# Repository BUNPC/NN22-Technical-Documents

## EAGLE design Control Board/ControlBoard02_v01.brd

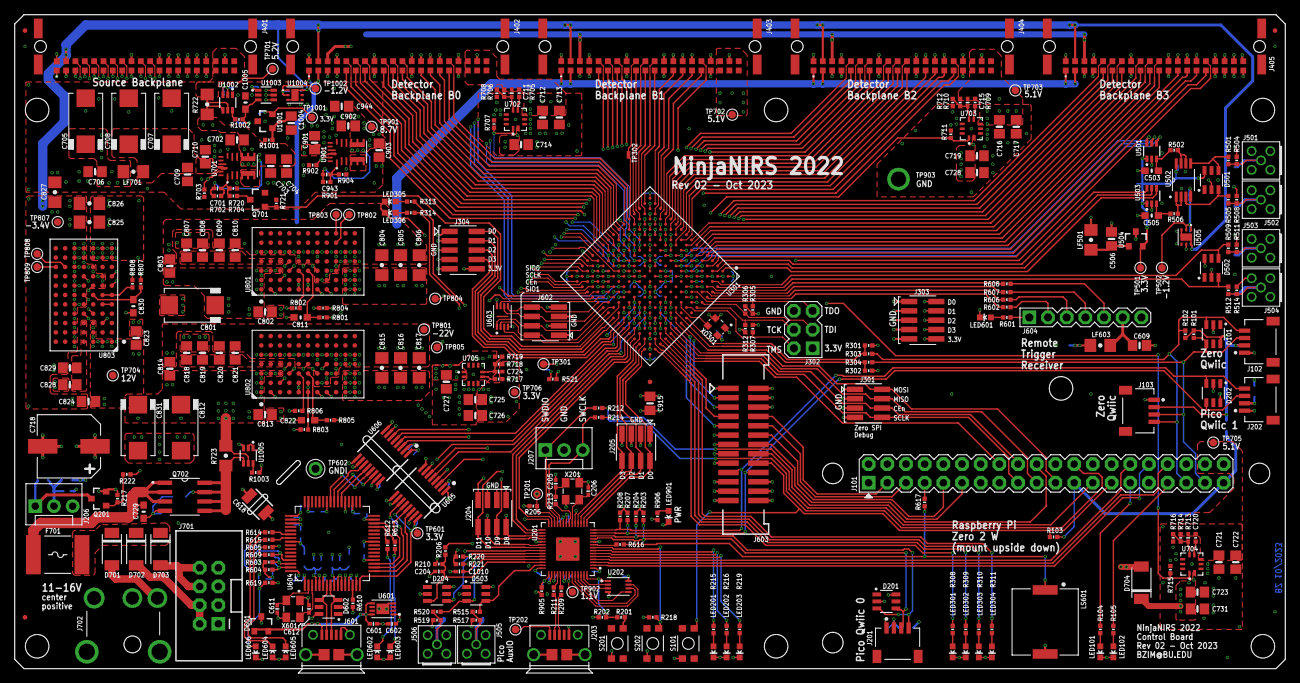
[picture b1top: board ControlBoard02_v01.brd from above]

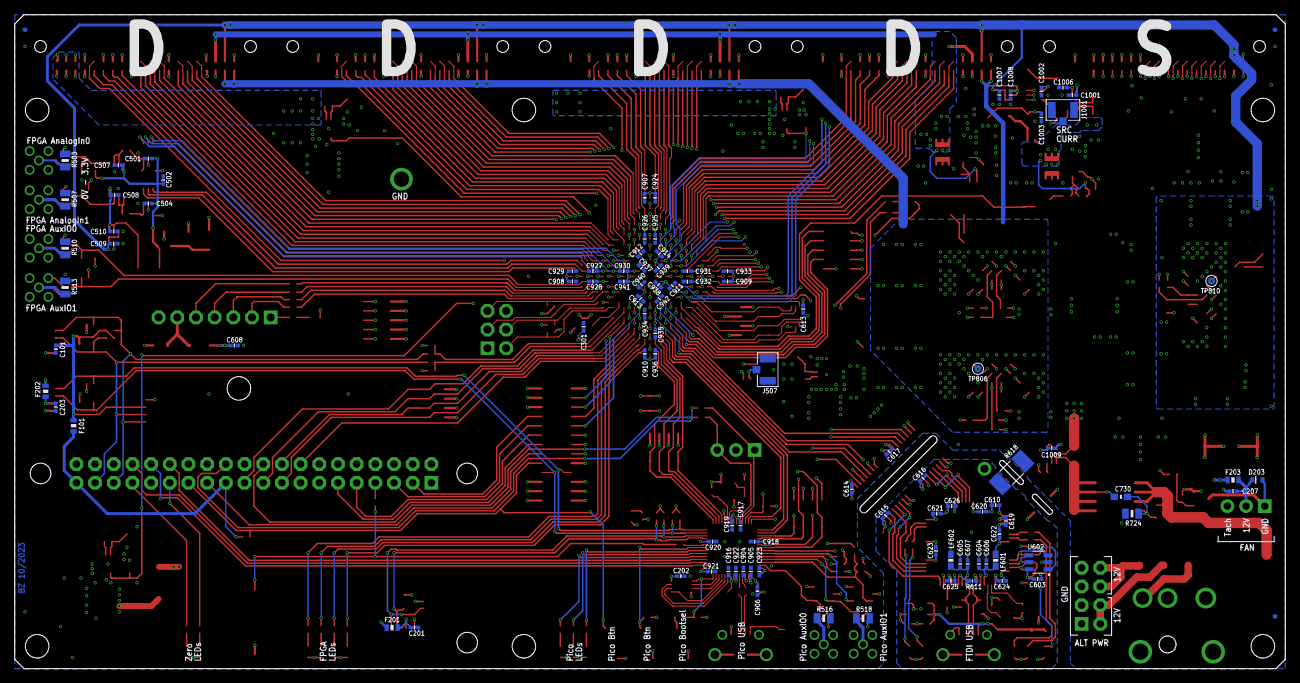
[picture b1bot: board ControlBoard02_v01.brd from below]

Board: 6 copper layers, 172.7 x 88.9 mm, 430 parts (103 on the bottom side), 365 nets.

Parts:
C101, C201, C202, C203, C204, C207, C301, C501, C504, C507, C508, C603, C606, C607, C608, C613, C614, C615, C616, C617, C619, C620, C621, C622, C623, C624, C625, C626, C916, C917, C918, C919, C920, C921, C922, C923, C924, C925, C926, C927, C928, C929, C930, C931, C932, C933, C934, C935, C936, C937, C938, C939, C940, C941, C942, C1001, C1002, C1006, C1009, C1010: 0.1u; 0402-CAP
C205, C206, C611, C612: 27p; 0402-CAP
C502, C509, C510, C601, C602, C604, C605, C610, C904, C905, C906, C907, C908, C909, C910, C911, C912, C913, C914, C1003, C1007, C1008: 4.7u; 0402-CAP
C503, C505, C729, C1005: 10n; 0603-CAP
C506, C609, C702, C703, C704, C706, C709, C710, C712, C713, C714, C716, C717, C719, C721, C722, C723, C725, C726, C727, C728, C731, C901, C902, C903, C944, C1004: 22u; 0805-CAP
C618: DNP; 1210
C701, C943: 22p; 0402-CAP
C705, C707, C708, C801, C812, C831: 100u/25V; 2917-CAP
C711, C715, C720, C724: 39p; 0402-CAP
C718: 330u/25V; CAP-SMD-POL-8X10
C730: 1n; 0603-CAP
C802, C803, C807, C808, C809, C810, C813, C814, C818, C819, C820, C821, C823, C824, C828, C829: 4.7u; 0805-CAP
C804, C805, C806, C815, C816, C817: 10u; 1206
C811, C822, C830: 1u; 0603-CAP
C825, C826: 100u; 1206
C827: DNP; 1206
C915: DNP; 0805-CAP
D101, D201, D202, D204, D501, D502, D503, D602: D1213A-02SO; SOT23-6
D203: SOD523
D601: PACDN042; SOT23-3
D701, D702, D703, D704: SOD128
F101, F201, F202, F203: 0ZCM0010FF2G; 0603-RES
F701: 2920L600/16MR; 2920-FUSE
FID901, FID902, FID903, FID904, FID905, FID906, FID907: FIDUCIALUFIDUCIAL; MICRO-FIDUCIAL
J101: M20X2_PTH
J102, J103, J201, J202: M04X1_JST_SH_RA; M04X1_JST_SH_SM_RA
J203, J601: USB-MICRO
J204, J205, J301, J602: M04X2_0.050_SMD_NO_CREAM
J206, J207: MOLEX-1X3
J302: M03X2PTH; 2X3-NS
J303, J304: M05X2_SMD_0.050_NOCREAM; M05X2_0.050_SMD_NO_CREAM
J401, J402, J403, J404, J405: M20X2_HARFLEX_M
J501, J502, J503, J504, J505, J506: SMA_MMCX_PTH_RA; MMCX_PTH_RA
J507, J1001: U.FL
J603: M13X2_0.050_SHF_NO_CREAM
J604: M07X1_PTH
J701: M04X2_SHROUDED; M04X2-SHROUDED
J702: POWERJACK_PJ051AH; PJ051AH
LED101, LED201, LED301, LED303, LED305, LED603, LED605, LED606, LED901: LTST-C191KRKT; LED-0603
LED102, LED202, LED203, LED302, LED304, LED306, LED601, LED602, LED604: LTST-C191KGKT; LED-0603
LF501, LF603, LF701: FERRITE1206; 1206
LF601, LF602: FERRITE0603; 0603-FER
LS601: PKMCS0909E4000-R1; XDCR_PKMCS0909E4000-R1
Q201, Q701: MOSFET-NCHANNELSMD; SOT23-3
Q702: MOSFET-PCHANNEL_SO8; SO08
R101, R102, R103, R203, R204, R207, R208, R210, R218, R301, R302, R305, R306, R307, R312, R504, R508, R511, R514, R517, R519, R603, R604, R605: 10k; 0402-RES
R104, R105, R215, R216, R219, R220, R222, R308, R309, R310, R311, R313, R314, R601, R1003: 470; 0402-RES
R201, R501, R505, R602, R606, R607, R608, R610, R612, R613, R614, R615, R616, R617, R619, R705, R709, R713, R717, R906: 1k; 0402-RES
R202, R212, R214, R303, R304: DNP; 0402-RES
R205, R217, R221, R703, R707, R711, R715, R721, R804, R902: 100k; 0402-RES
R206, R702, R706, R710, R714, R718, R901: 47k; 0402-RES
R209, R211: 27; 0402-RES
R213: 1.2k; 0402-RES
R502, R506, R801, R805: 82; 0402-RES
R503, R507, R510, R513, R516, R518: DNP; 0805
R509, R512, R515, R520, R521, R905, R1002: 100; 0402-RES
R609, R904: 3.48k; 0402-RES
R611: 12k; 0402-RES
R618: 1M; R2010
R704, R720: 6.2k; 0402-RES
R708, R712, R716: 8.66k; 0402-RES
R719: 15k; 0402-RES
R722, R723: 0.01; 1206
R724: 10M; 0805
R802, R806: 180k; 0402-RES
R803: 220k; 0402-RES
R807, R1001: 15; 0402-RES
R808: 68k; 0402-RES
S101, S201, S202: SWITCH-MOMENTARY-2SMD-3; TACTILE_SWITCH_SMD-3
TP201, TP202, TP301, TP501, TP502, TP601, TP701, TP702, TP703, TP704, TP705, TP706, TP801, TP802, TP803, TP804, TP805, TP806, TP807, TP808, TP809, TP810, TP901, TP902, TP1001, TP1002: TESTPOINT_ROUND; TESTPAD_ROUND
TP302: TESTPOINTPADSMALL; TESTPAD_SMALL
TP602: TESTPOINT1X01; 1X01
TP903: TESTPOINTTUR; TURRET
U201: RP2040; QFN-56_EP
U202: W25Q_USON; USON8L-2X3MM
U301: MACHXO2_FTBGA256; LBGA-256
U501, U503, U1003: ADS7886; SOT363
U502: LT1801; SOP65P490X110-8N
U504, U1001: REF30XX; SOT23-3
U505, U1004: ADP7182_WSON; WSON6
U601: MCP1755_DFN; DFN8_2X3MM
U602: 93LC56; SOT23-6
U603: APS6404L_PAD; USON8L-2X3MM_APM
U604: FT2232H_QFP; QFP50P1200X1200X160-64N
U605, U606: ISO7742_DBQ; SSOP16
U701, U901: MPM3630_FULL_CREAM; QFN-20-MPS_FULL_CREAM
U702, U703, U704, U705: RPL-30
U801, U802, U803: LTM4651; BGA-77
U1002, U1005: INA21X_DCK; SOT363
X201, X601: 403I35D12M00000; CRYSTAL-3.2-2.5
XO301: OSCILLATOR_TXO2520; TXO2520

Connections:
ADS_CSN0: U301.H5, U501.6
ADS_CSN1: U301.C1, U503.6
ADS_CSN2: U301.K12, U1003.6
ADS_SCK0: U301.F5, U501.4
ADS_SCK1: U301.B1, U503.4
ADS_SCK2: U301.J12, U1003.4
ADS_SDO0: U301.G5, U501.5
ADS_SDO1: U301.C2, U503.5
ADS_SDO2: U301.K14, U1003.5
AUXIO0: D502.4, R509.2, U301.B3
AUXIO1: D502.3, R512.2, U301.A3
AUXIO2: R521.2, U301.H13
BOOTSEL: R201.1, S201.4
DETB_END_CYC0: J402.B15, U301.R7
DETB_END_CYC1: J403.B15, U301.P1
DETB_END_CYC2: J404.B15, U301.J1
DETB_END_CYC3: J405.B15, U301.D1
DETB_RUN0: J402.A16, U301.T5
DETB_RUN1: J403.A16, U301.N3
DETB_RUN2: J404.A16, U301.K5
DETB_RUN3: J405.A16, U301.E3
DETB_SELECT00: J402.B11, U301.R9
DETB_SELECT01: J402.B9, U301.R11
DETB_SELECT02: J402.A10, U301.T9
DETB_SELECT03: J402.B7, U301.N9
DETB_SELECT04: J402.B5, U301.N11
DETB_SELECT05: J402.A6, U301.P9
DETB_SELECT06: J403.B11, U301.T2
DETB_SELECT07: J403.B9, U301.T4
DETB_SELECT08: J403.A10, U301.R4
DETB_SELECT09: J403.B7, U301.P5
DETB_SELECT10: J403.B5, U301.N8
DETB_SELECT11: J403.A6, U301.N6
DETB_SELECT12: J404.B11, U301.K2
DETB_SELECT13: J404.B9, U301.M2
DETB_SELECT14: J404.A10, U301.M1
DETB_SELECT15: J404.B7, U301.J4
DETB_SELECT16: J404.B5, U301.L4
DETB_SELECT17: J404.A6, U301.L3
DETB_SELECT18: J405.B11, U301.F2
DETB_SELECT19: J405.B9, U301.H2
DETB_SELECT20: J405.A10, U301.G1
DETB_SELECT21: J405.B7, U301.F4
DETB_SELECT22: J405.B5, U301.H4
DETB_SELECT23: J405.A6, U301.G3
DETB_STATUS_SELECT0: J402.B16, U301.R6
DETB_STATUS_SELECT1: J403.B16, U301.N2
DETB_STATUS_SELECT2: J404.B16, U301.J2
DETB_STATUS_SELECT3: J405.B16, U301.D2
DETB_TRIGGER0: J402.B14, U301.T7
DETB_TRIGGER1: J403.B14, U301.P2
DETB_TRIGGER2: J404.B14, U301.J3
DETB_TRIGGER3: J405.B14, U301.E2
EXP_J303_D0: J303.2, U301.C5
EXP_J303_D1: J303.4, U301.D6
EXP_J303_D2: J303.6, U301.D7
EXP_J303_D3: J303.8, U301.C7
EXP_J304_D0: J304.2, U301.H16
EXP_J304_D1: J304.4, U301.H15
EXP_J304_D2: J304.6, U301.G16
EXP_J304_D3: J304.8, U301.G15
EXP_J601_D0: J603.3, U301.C10
EXP_J601_D1: J603.5, U301.B10
EXP_J601_D2: J603.7, U301.A13
EXP_J601_D3: J603.9, U301.E10
EXP_J601_D4: J603.11, U301.D11
EXP_J601_D5: J603.13, U301.C12
EXP_J601_D6: J603.15, U301.C13
FAN_NEW: R222.1, U201.36
FAN_SENSE: D204.4, R220.1, U201.37
FP_LED0: R308.2, U301.A15
FP_LED1: R309.2, U301.B14
FP_LED2: R310.2, U301.A14
FP_LED3: R311.2, U301.B13
FP_LED4: R313.2, U301.K13
FP_LED5: R314.2, U301.J13
FP_SCL: R301.1, R303.1, U301.A9
FP_SDA: R302.1, R304.1, U301.C9
FTA_CTS#: U604.19, U605.13
FTA_RTS#: U604.18, U605.11
FTA_RXD: U604.17, U605.14
FTA_RXLED#: R612.1, U604.29
FTA_TXD: U604.16, U605.12
FTA_TXLED#: R613.1, U604.30
FTB_CTS#: U604.41, U606.13
FTB_RTS#: U604.40, U606.11
FTB_RXD: U604.39, U606.14
FTB_RXLED#: R614.1, U604.54
FTB_TXD: U604.38, U606.12
FTB_TXLED#: R615.1, U604.55
FT_VREGOUT: C610.1, C624.1, C625.1, C626.1, U604.12, U604.37, U604.49, U604.64
GND: C101.2, C201.2, C202.2, C203.2, C204.2, C205.2, C206.2, C207.2, C301.2, C501.2, C502.2, C503.2, C504.2, C505.2, C506.2, C507.2, C508.1, C509.1, C510.1, C608.2, C609.2, C613.2, C614.2, C617.2, C618.1, C702.2, C703.2, C704.2, C705.N, C706.2, C707.N, C708.N, C709.2, C710.2, C712.2, C713.2, C714.2, C716.2, C717.2, C718.N, C719.2, C721.2, C722.2, C723.2, C725.2, C726.2, C727.2, C728.2, C731.2, C801.N, C802.2, C804.1, C805.1, C806.1, C807.2, C808.2, C812.N, C813.2, C815.1, C816.1, C817.1, C818.2, C819.2, C823.2, C825.1, C826.1, C827.1, C828.2, C831.N, C901.2, C902.2, C903.2, C904.2, C905.2, C906.2, C907.2, C908.2, C909.2, C910.2, C911.2, C912.2, C913.2, C914.2, C915.2, C916.2, C917.2, C918.2, C919.2, C920.2, C921.2, C922.2, C923.2, C924.2, C925.2, C926.2, C927.2, C928.2, C929.2, C930.2, C931.2, C932.2, C933.2, C934.2, C935.2, C936.2, C937.2, C938.2, C939.2, C940.2, C941.2, C942.2, C944.2, C1001.2, C1002.2, C1003.2, C1004.2, C1005.2, C1006.2, C1007.1, C1008.1, C1009.2, C1010.2, D101.2, D201.2, D202.2, D204.2, D501.2, D502.2, D503.2, J101.1, J101.8, J101.12, J101.15, J101.22, J101.28, J101.31, J101.36, J102.1, J103.1, J201.1, J202.1, J203.5, J203.SH1, J203.SH2, J203.SH3, J203.SH4, J203.SH5, J203.SH6, J204.1, J204.3, J204.5, J204.7, J205.1, J205.3, J205.5, J205.7, J207.2, J301.1, J301.3, J301.5, J301.7, J302.6, J303.1, J303.3, J303.5, J303.7, J303.9, J304.1, J304.3, J304.5, J304.7, J304.9, J401.A1, J401.A9, J401.A12, J401.A13, J401.A14, J401.A15, J401.A16, J401.A17, J401.A19, J401.B1, J401.B2, J401.B3, J401.B17, J402.A1, J402.A4, J402.A8, J402.A12, J402.A13, J402.A14, J402.A15, J402.A17, J402.A19, J402.B3, J402.B4, J402.B8, J402.B12, J402.B17, J403.A1, J403.A4, J403.A8, J403.A12, J403.A13, J403.A14, J403.A15, J403.A17, J403.A19, J403.B3, J403.B4, J403.B8, J403.B12, J403.B17, J404.A1, J404.A4, J404.A8, J404.A12, J404.A13, J404.A14, J404.A15, J404.A17, J404.A19, J404.B3, J404.B4, J404.B8, J404.B12, J404.B17, J405.A1, J405.A4, J405.A8, J405.A12, J405.A13, J405.A14, J405.A15, J405.A17, J405.A19, J405.B3, J405.B4, J405.B8, J405.B12, J405.B17, J501.G@1, J501.G@2, J501.G@3, J501.G@4, J502.G@1, J502.G@2, J502.G@3, J502.G@4, J503.G@1, J503.G@2, J503.G@3, J503.G@4, J504.G@1, J504.G@2, J504.G@3, J504.G@4, J505.G@1, J505.G@2, J505.G@3, J505.G@4, J506.G@1, J506.G@2, J506.G@3, J506.G@4, J507.P$1, J507.P$2, J602.1, J602.3, J602.5, J602.7, J603.1, J603.2, J603.4, J603.6, J603.17, J603.21, J603.24, J603.25, J604.7, J701.1, J701.3, J701.5, J701.7, J702.SHIELD1, J702.SHIELD2, J702.SLEEVE, J702.SWITCH, J1001.P$1, J1001.P$2, LED101.C, LED102.C, LED201.C, LED202.C, LED203.C, LED301.C, LED302.C, LED303.C, LED304.C, LED305.C, LED306.C, LED601.C, LED901.C, LS601.2, Q201.2, Q701.2, R210.1, R217.1, R218.1, R312.1, R503.1, R504.1, R507.1, R508.1, R510.1, R511.1, R513.1, R514.1, R516.1, R517.1, R518.1, R519.1, R618.1, R703.1, R707.1, R708.1, R711.1, R712.1, R715.1, R716.1, R719.1, R720.1, R721.1, R724.1, R801.2, R804.2, R805.2, R807.2, R902.1, R904.1, S101.1, S201.1, TP903.P$1, U201.19, U201.PAD, U202.4, U301.B2, U301.B15, U301.C3, U301.C14, U301.D4, U301.D13, U301.E5, U301.E12, U301.F6, U301.F11, U301.H8, U301.H9, U301.J8, U301.J9, U301.L6, U301.L11, U301.M5, U301.M12, U301.N4, U301.N13, U301.P3, U301.P14, U301.R2, U301.R15, U501.2, U503.2, U504.3, U505.5, U603.4, U605.2, U605.8, U606.2, U606.8, U701.3, U701.12, U701.13, U701.14, U702.3, U702.4, U702.8, U703.3, U703.4, U703.8, U704.3, U704.4, U704.8, U705.3, U705.4, U705.8, U801.D4, U801.G1, U801.H1, U801.K1, U801.K2, U801.K3, U801.L1, U801.L2, U801.L3, U802.D4, U802.G1, U802.H1, U802.K1, U802.K2, U802.K3, U802.L1, U802.L2, U802.L3, U803.D4, U803.G1, U803.H1, U803.K1, U803.K2, U803.K3, U803.L1, U803.L2, U803.L3, U901.3, U901.12, U901.13, U901.14, U1001.3, U1002.1, U1003.2, U1004.5, U1005.1, U1005.2, X201.2, X201.4, XO301.2
GNDI: C601.2, C602.2, C603.2, C604.2, C605.2, C606.2, C607.2, C610.2, C611.2, C612.2, C615.2, C616.2, C618.2, C619.2, C620.2, C621.2, C622.2, C623.2, C624.2, C625.2, C626.2, D601.3, D602.2, J601.5, J601.SH1, J601.SH2, J601.SH3, J601.SH4, J601.SH5, J601.SH6, LED606.C, R611.1, R618.2, TP602.1, U601.4, U601.P, U602.2, U604.1, U604.5, U604.10, U604.11, U604.13, U604.15, U604.25, U604.35, U604.47, U604.51, U605.9, U605.15, U606.9, U606.15, X601.2, X601.4
LED: J604.1, R601.1
unnamed: U803.D3, U803.G3
unnamed: TP802.P$1, U801.J6
unnamed: C701.2, R702.1, R704.2, R720.2, U701.1
unnamed: Q701.3, R704.1
unnamed: U803.E1, U803.E2
unnamed: U801.D3, U801.G3
unnamed: U801.E1, U801.E2, U802.E1, U802.E2
unnamed: C1005.1, J1001.P$3, R1002.2, U1003.3
unnamed: R802.2, U801.E3
unnamed: D701.A, J702.CENTER
unnamed: TP803.P$1, U801.J7
unnamed: C811.1, R801.1, U801.F3
unnamed: LED606.A, R619.1
unnamed: LED901.A, R906.1
unnamed: C206.1, U201.20, X201.3
unnamed: C205.1, R213.2, X201.1
unnamed: R213.1, U201.21
unnamed: C822.1, R805.1, U802.F3
unnamed: TP808.P$1, U803.J6
unnamed: TP809.P$1, U803.J7
unnamed: R803.1, U801.F1, U801.F2, U802.F1, U802.F2
unnamed: U802.D3, U802.G3
unnamed: R604.1, U602.5, U604.63
unnamed: TP806.P$1, U802.H4
unnamed: C830.1, R807.1, U803.F3
unnamed: C807.1, C808.1, C809.1, C810.1, U801.A4, U801.B4, U801.C4
unnamed: C711.2, R706.1, R708.2, U702.7
unnamed: R209.1, U201.47
unnamed: R211.1, U201.46
unnamed: C818.1, C819.1, C820.1, C821.1, U802.A4, U802.B4, U802.C4
unnamed: R806.2, U802.E3
unnamed: R705.1, U702.6
unnamed: C715.2, R710.1, R712.2, U703.7
unnamed: J203.2, R211.2
unnamed: R808.1, U803.F1, U803.F2
unnamed: J203.3, R209.2
unnamed: R709.1, U703.6
unnamed: TP810.P$1, U803.H4
unnamed: C720.2, R714.1, R716.2, U704.7
unnamed: C828.1, C829.1, U803.A4, U803.B4, U803.C4
unnamed: R713.1, U704.6
unnamed: C906.1, R905.2, U201.43
unnamed: C724.2, R718.1, R719.2, U705.7
unnamed: R717.1, U705.6
unnamed: J501.C, R501.1, R503.2, R504.2
unnamed: D501.4, R501.2, U502.5
unnamed: J502.C, R505.1, R507.2, R508.2
unnamed: D501.3, R505.2, U502.3
unnamed: R603.1, U602.4, U604.62
unnamed: R1002.1, U1002.6
unnamed: C1004.1, R1001.2, U1001.1
unnamed: J505.C, R515.1, R516.2, R517.2
unnamed: R605.1, R609.1, U602.1
unnamed: LED301.A, R308.1
unnamed: LED302.A, R309.1
unnamed: LED303.A, R310.1
unnamed: LED304.A, R311.1
unnamed: LS601.1, R616.1, R617.1
unnamed: J503.C, R509.1, R510.2, R511.2
unnamed: R609.2, U602.3, U604.61
unnamed: J504.C, R512.1, R513.2, R514.2
unnamed: LED203.A, R219.1
unnamed: C605.1, C607.1, LF602.2, U604.9
unnamed: C604.1, C606.1, LF601.2, U604.4
unnamed: C943.2, R901.1, R904.2, U901.1
unnamed: R610.2, U604.14
unnamed: R611.2, U604.6
unnamed: C611.1, U604.2, X601.1
unnamed: C612.1, U604.3, X601.3
unnamed: LED604.C, R614.2
unnamed: LED605.C, R615.2
unnamed: LED602.C, R612.2
unnamed: C503.1, R502.2, U501.3
unnamed: R502.1, U502.6, U502.7
unnamed: LED603.C, R613.2
unnamed: R1003.1, U1005.6
unnamed: C505.1, R506.2, U503.3
unnamed: R506.1, U502.1, U502.2
unnamed: D702.A, J701.2, J701.4
unnamed: C729.1, F701.2, Q702.1, Q702.2, Q702.3
unnamed: J206.3, R220.2, R221.1
unnamed: LED305.A, R313.1
unnamed: LED202.A, R216.1
unnamed: LED101.A, R104.1
unnamed: D703.A, J701.6, J701.8
unnamed: LED102.A, R105.1
unnamed: D701.C, D702.C, D703.C, F701.1
unnamed: LED306.A, R314.1
unnamed: LED201.A, R215.1
unnamed: D203.A, J206.1, Q201.3
unnamed: C729.2, C730.2, Q702.4, R724.2
unnamed: J507.P$3, R521.1
unnamed: J506.C, R518.2, R519.2, R520.1
unnamed: C506.1, LF501.2, U504.1
unnamed: Q201.1, R217.2, R222.2
unnamed: D602.3, J601.3, U604.8
unnamed: D602.4, J601.2, U604.7
unnamed: J604.5, R608.2
unnamed: J604.4, R607.2
unnamed: J604.3, R606.2
unnamed: J604.2, R602.2
unnamed: LED601.A, R601.2
OSC_CLK: U301.C8, XO301.3
QSPI_SCLK: U201.52, U202.6
QSPI_SD0: U201.53, U202.5
QSPI_SD1: U201.55, U202.2
QSPI_SD2: U201.54, U202.3
QSPI_SD3: U201.51, U202.7
QSPI_SS_N: R201.2, R202.1, U201.56, U202.1
RAM0_CEN: J602.4, U301.K16, U603.1
RAM0_SCLK: J602.6, U301.K15, U603.6
RAM0_SIO0: J602.8, U301.L16, U603.5
RAM0_SIO1: J602.2, U301.J15, U603.2
RAM0_SIO2: U301.J16, U603.3
RAM0_SIO3: U301.L15, U603.7
RPFP_D0: J205.2, U201.15, U301.B16
RPFP_D1: J205.4, U201.16, U301.C15
RPFP_D2: J205.6, U201.17, U301.C16
RPFP_D3: J205.8, U201.18, U301.D15
RPFP_D4: U201.27, U301.D16
RPFP_D5: U201.28, U301.E14
RPFP_D6: U201.29, U301.E15
RPFP_D7: U201.30, U301.E16
RPFP_D8: J204.2, U201.31, U301.T6
RPFP_D9: J204.4, U201.32, U301.R12
RPFP_D10: J204.6, U201.34, U301.P6
RPFP_D11: J204.8, U201.35, U301.P13
RPFP_RUN: R205.1, TP201.P$1, U201.26, U301.H12
RPI0_BUZZ: J101.7, R617.2
RPI0_CE: J101.18, J301.6, U301.B11
RPI0_GPIO5: J101.11, J603.14
RPI0_GPIO6: J101.9, J603.12
RPI0_GPIO7: J101.16, U301.B12
RPI0_GPIO12: J101.10, U301.D9
RPI0_GPIO16: J101.6, U301.E9
RPI0_GPIO18: J101.30, U201.4
RPI0_GPIO19: J101.5, J603.10
RPI0_GPIO20: J101.4, U301.D10
RPI0_GPIO21: J101.2, U301.C11
RPI0_GPIO22: J101.25, J603.16
RPI0_GPIO24: J101.24, R212.1
RPI0_GPIO25: J101.20, R214.1
RPI0_GPIO26: J101.3, J603.8
RPI0_GPIO27: J101.27, J603.18, R103.1, S101.4
RPI0_LED0: J101.29, R104.2
RPI0_LED1: J101.33, R105.2
RPI0_MISO: J101.19, J301.4, U301.A11
RPI0_MOSI: J101.21, J301.2, U301.A10
RPI0_RX0: J101.32, U201.2
RPI0_SCL: D101.3, J101.35, J102.4, J103.4, R102.1, R303.2
RPI0_SCLK: J101.17, J301.8, U301.A12
RPI0_SDA: D101.4, J101.37, J102.3, J103.3, R101.1, R304.2
RPI0_TX0: J101.34, U201.3
RPI0_V3P3: F101.2, J101.23, J101.39, R103.2
RPIP_AUXIO0: D503.4, R515.2, U201.41
RPIP_AUXIO1: D503.3, R520.2, U201.39
RPIP_BTN: R218.2, S202.1, U201.8
RPIP_BUZZ: R616.2, U201.9
RPIP_LED0: R215.2, U201.7
RPIP_LED1: R216.2, U201.6
RPIP_LED2: R219.2, U201.5
RPIP_SCL0: D201.3, J201.4, R204.1, U201.12
RPIP_SCL1: D202.3, J202.4, J603.19, R208.1, U201.14
RPIP_SDA0: D201.4, J201.3, R203.1, U201.11
RPIP_SDA1: D202.4, J202.3, J603.20, R207.1, U201.13
SRC_COL00: J401.A11, U301.M10
SRC_COL01: J401.A10, U301.T12
SRC_COL02: J401.A8, U301.R13
SRC_COL03: J401.A7, U301.R14
SRC_COL04: J401.A6, U301.R16
SRC_COL05: J401.A5, U301.P16
SRC_COL06: J401.B8, U301.T14
SRC_COL07: J401.B7, U301.T15
SRC_COL08: J401.A4, U301.N15
SRC_COL09: J401.A3, U301.M14
SRC_COL10: J401.B10, U301.P12
SRC_COL11: J401.B9, U301.T13
SRC_COL12: J401.B12, U301.M11
SRC_COL13: J401.B11, U301.L10
SRC_PWR0: J401.B6, U301.P15
SRC_PWR1: J401.B5, U301.N14
SRC_PWR2: J401.B4, U301.N16
SRC_ROW0: J401.B16, U301.L9
SRC_ROW1: J401.B15, U301.M9
SRC_ROW2: J401.B14, U301.P11
SRC_SPARE: J401.B13, U301.T11
SWCLK: J207.3, R214.2, U201.24
SWDIO: J207.1, R212.2, U201.25
TCK: J302.4, R312.2, U301.A7
TDI: J302.3, R306.1, U301.A6
TDO: J302.5, R305.1, U301.C6
TMS: J302.2, R307.1, U301.B8
TRG0: R608.1, U301.B4
TRG1: R607.1, U301.A4
TRG2: R606.1, U301.B5
TRG3: R602.1, U301.A5
UARTB_CTSN_TO_FTDI: U301.G13, U606.4
UARTB_FPGA_TO_FTDI: U301.F16, U606.3
UARTB_FTDI_TO_FPGA: U301.G12, U606.5
UARTB_RTSN_TO_FPGA: U301.G14, U606.6
UART_CTSN_TO_FTDI: U301.F15, U605.4
UART_DETB_TO_FPGA00: J402.B10, U301.R10
UART_DETB_TO_FPGA01: J402.A11, U301.T8
UART_DETB_TO_FPGA02: J402.A9, U301.T10
UART_DETB_TO_FPGA03: J402.B6, U301.N10
UART_DETB_TO_FPGA04: J402.A7, U301.P8
UART_DETB_TO_FPGA05: J402.A5, U301.P10
UART_DETB_TO_FPGA06: J403.B10, U301.T3
UART_DETB_TO_FPGA07: J403.A11, U301.R3
UART_DETB_TO_FPGA08: J403.A9, TP302.P$1, U301.R5
UART_DETB_TO_FPGA09: J403.B6, U301.N7
UART_DETB_TO_FPGA10: J403.A7, U301.P4
UART_DETB_TO_FPGA11: J403.A5, U301.P7
UART_DETB_TO_FPGA12: J404.B10, U301.L2
UART_DETB_TO_FPGA13: J404.A11, U301.L1
UART_DETB_TO_FPGA14: J404.A9, U301.N1
UART_DETB_TO_FPGA15: J404.B6, U301.K4
UART_DETB_TO_FPGA16: J404.A7, U301.K3
UART_DETB_TO_FPGA17: J404.A5, U301.M3
UART_DETB_TO_FPGA18: J405.B10, U301.G2
UART_DETB_TO_FPGA19: J405.A11, U301.F1
UART_DETB_TO_FPGA20: J405.A9, U301.H1
UART_DETB_TO_FPGA21: J405.B6, U301.G4
UART_DETB_TO_FPGA22: J405.A7, U301.F3
UART_DETB_TO_FPGA23: J405.A5, U301.H3
UART_FPGA_TO_DETB0: J402.B13, U301.R8
UART_FPGA_TO_DETB1: J403.B13, U301.R1
UART_FPGA_TO_DETB2: J404.B13, U301.K1
UART_FPGA_TO_DETB3: J405.B13, U301.E1
UART_FPGA_TO_FTDI: U301.F14, U605.3
UART_FTDI_TO_FPGA: U301.F12, U605.5
UART_FTDI_TXLEDN: TP301.P$1, U301.H14
UART_RTSN_TO_FPGA: U301.F13, U605.6
V1P1: C904.1, C916.1, C917.1, TP902.P$1, U201.23, U201.45, U201.50
V3P3: C202.1, C301.1, C608.1, C613.1, C614.1, C617.1, C724.1, C725.1, C726.1, C905.1, C907.1, C908.1, C909.1, C910.1, C911.1, C912.1, C913.1, C914.1, C915.1, C918.1, C919.1, C920.1, C921.1, C922.1, C923.1, C924.1, C925.1, C926.1, C927.1, C928.1, C929.1, C930.1, C931.1, C932.1, C933.1, C934.1, C935.1, C936.1, C937.1, C938.1, C939.1, C940.1, C941.1, C942.1, C1009.1, D201.6, D202.6, D204.6, D502.6, D503.6, F201.1, F202.1, J302.1, J303.10, J304.10, J603.22, J603.23, LF603.1, R202.2, R203.2, R204.2, R205.2, R207.2, R208.2, R221.2, R301.2, R302.2, R305.2, R306.2, R307.2, R717.2, R718.2, R905.1, R906.2, S202.4, TP706.P$1, U201.1, U201.10, U201.22, U201.33, U201.42, U201.44, U201.48, U201.49, U202.8, U301.A1, U301.A16, U301.D5, U301.D12, U301.E4, U301.E13, U301.G7, U301.G8, U301.G9, U301.G10, U301.H7, U301.H10, U301.J7, U301.J10, U301.K7, U301.K8, U301.K9, U301.K10, U301.M4, U301.M13, U301.N5, U301.N12, U301.T1, U301.T16, U603.8, U605.1, U605.7, U606.1, U606.7, U705.5, U1005.3, XO301.1, XO301.4
V3P3_J102: C101.1, D101.6, F101.1, J102.2, J103.2, R101.2, R102.2
V3P3_J201: C201.1, F201.2, J201.2
V3P3_J202: C203.1, F202.2, J202.2
V3P3_R: C609.1, J604.6, LF603.2
V3P3_USB: C602.1, C603.1, C615.1, C616.1, C619.1, C620.1, C621.1, C622.1, C623.1, D602.6, LED602.A, LED603.A, LED604.A, LED605.A, LF601.1, LF602.1, R603.2, R604.2, R605.2, R610.1, R619.2, TP601.P$1, U601.1, U602.6, U604.20, U604.31, U604.42, U604.50, U604.56, U605.10, U605.16, U606.10, U606.16
V5P0_USB: C601.1, D601.1, D601.2, J601.1, U601.5, U601.8
V5P1_B01: C711.1, C712.1, C713.1, J402.A18, J402.A20, J402.B18, J402.B19, J402.B20, J403.A18, J403.A20, J403.B18, J403.B19, J403.B20, R705.2, R706.2, TP702.P$1, U702.5
V5P1_B01_EN: R707.2, U301.M7, U702.1
V5P1_B23: C715.1, C716.1, C717.1, J404.A18, J404.A20, J404.B18, J404.B19, J404.B20, J405.A18, J405.A20, J405.B18, J405.B19, J405.B20, LF501.1, R709.2, R710.2, TP703.P$1, U703.5
V5P1_B23_EN: R711.2, U301.J5, U703.1
V5P1_RPI: C720.1, C721.1, C722.1, J101.38, J101.40, R713.2, R714.2, TP705.P$1, U704.5
V5P1_RPI_EN: R715.2, U301.B7, U704.1
V5P1_SRC: J401.A18, J401.A20, J401.B18, J401.B19, J401.B20, R722.2, TP701.P$1, U1002.5
V5P1_SRC_EN: R703.2, U301.L8, U701.17
V5P1_SRC_PRE: C701.1, C702.1, C703.1, C704.1, R702.2, R722.1, R1001.1, U701.7_8_9, U1002.4
V9P0: C902.1, C903.1, C943.1, C944.1, J402.A3, J403.A3, J404.A3, J405.A3, R901.2, TP901.P$1, U901.7_8_9
V9P0_EN: R902.2, U301.M8, U901.17
V12: C705.P, C706.1, C714.1, C718.P, C719.1, C727.1, C728.1, C801.P, C802.1, C803.1, C812.P, C813.1, C814.1, C823.1, C824.1, C831.P, C901.1, D704.A, F203.1, J603.26, LF701.1, R206.2, R723.2, TP704.P$1, U702.2, U703.2, U705.1, U705.2, U801.A1, U801.A2, U801.A3, U801.B3, U801.C3, U802.A1, U802.A2, U802.A3, U802.B3, U802.C3, U803.A1, U803.A2, U803.A3, U803.B3, U803.C3, U901.16, U1005.5
V12_CURR_SENSE: C1010.1, R1003.2, U201.38
V12_FAN: C207.1, D203.C, F203.2, J206.2
V12_PRE: C730.1, Q702.5, Q702.6, Q702.7, Q702.8, R723.1, U1005.4
V12_RPI: C723.1, C731.1, D704.C, U704.2
V12_SRC: C707.P, C708.P, C709.1, C710.1, LF701.2, U701.16
VA2_3P3: C1001.1, C1002.1, C1003.1, TP1001.P$1, U1001.2, U1002.3, U1003.1
VA_3P3: C501.1, C502.1, C504.1, C507.1, D501.6, TP501.P$1, U501.1, U502.8, U503.1, U504.2
VBUS: J203.1, TP202.P$1
VIN_SENSE: C204.1, D204.3, R206.1, R210.2, U201.40
VN1P2: C508.2, C510.2, TP502.P$1, U502.4, U505.1, U505.2
VN1P2_A2: C1006.1, C1008.2, TP1002.P$1, U1002.2, U1004.1, U1004.2
VN3P4: C509.2, C824.2, C825.2, C826.2, C827.2, C829.2, C830.2, C1007.2, J401.A2, J402.A2, J403.A2, J404.A2, J405.A2, R808.2, TP807.P$1, U505.3, U505.6, U505.PAD, U803.A5, U803.B5, U803.C2, U803.C5, U803.D5, U803.E4, U803.E5, U803.F5, U803.G2, U803.G4, U803.G5, U803.H2, U803.H3, U803.H5, U803.J3, U803.J4, U803.J5, U803.K4, U803.K5, U803.L4, U803.L5, U1004.3, U1004.6, U1004.PAD
VN3P4_EN: U301.L14, U803.F4
VN22: C803.2, C804.2, C805.2, C806.2, C809.2, C810.2, C811.2, C814.2, C815.2, C816.2, C817.2, C820.2, C821.2, C822.2, J402.B1, J402.B2, J403.B1, J403.B2, J404.B1, J404.B2, J405.B1, J405.B2, R802.1, R803.2, R806.1, TP801.P$1, U801.A5, U801.B5, U801.C2, U801.C5, U801.D5, U801.E4, U801.E5, U801.F5, U801.G2, U801.G4, U801.G5, U801.H2, U801.H3, U801.H5, U801.J3, U801.J4, U801.J5, U801.K4, U801.K5, U801.L4, U801.L5, U802.A5, U802.B5, U802.C2, U802.C5, U802.D5, U802.E4, U802.E5, U802.F5, U802.G2, U802.G4, U802.G5, U802.H2, U802.H3, U802.H5, U802.J3, U802.J4, U802.J5, U802.K4, U802.K5, U802.L4, U802.L5
VN22_CLKA: TP804.P$1, U301.M15, U801.B1
VN22_CLKB: TP805.P$1, U301.M16, U802.B1
VN22_EN: R804.1, U301.L13, U801.F4, U802.F4
V_SRC_BOOST: Q701.1, R721.2, U301.J14

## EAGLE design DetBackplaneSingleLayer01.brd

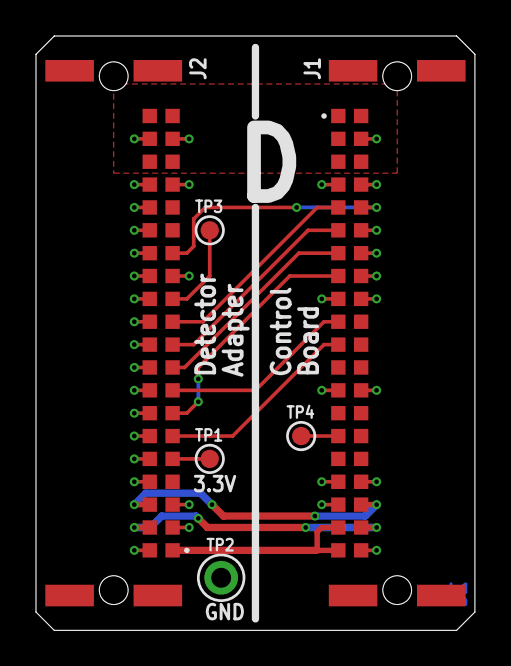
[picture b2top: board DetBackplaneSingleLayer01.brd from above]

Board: 2 copper layers, 24.4 x 33.0 mm, 6 parts (0 on the bottom side), 15 nets.

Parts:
J1, J2: M20X2_HARFLEX_M
TP1, TP3, TP4: TESTPOINT_ROUND; TESTPAD_ROUND
TP2: TESTPOINT1X01; 1X01

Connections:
DET_C0: J1.B5, J2.B11
DET_C1: J1.B6, J2.B10
DET_C2: J1.B7, J2.B9
DET_C3: J1.B8, J2.B7
DET_D0: J1.B10, J2.B8
DET_D1: J1.B11, J2.B6
DET_D7: J1.B15, TP4.P$1
DET_RUN: J1.A5, J2.B14
GND: J1.A2, J1.A4, J1.A6, J1.A7, J1.A8, J1.A9, J1.A13, J1.A17, J1.A20, J1.B4, J1.B9, J1.B13, J1.B17, J1.B18, J2.A1, J2.A4, J2.A5, J2.A6, J2.A7, J2.A8, J2.A9, J2.A10, J2.A11, J2.A12, J2.A13, J2.A14, J2.A15, J2.A16, J2.A17, J2.A19, J2.B2, J2.B3, J2.B13, J2.B17, J2.B19, TP2.1
unnamed: J2.B12, TP3.P$1
V3P3: J2.B5, TP1.P$1
V5P1: J1.A1, J1.A3, J1.B1, J1.B2, J1.B3, J2.A18, J2.A20, J2.B18, J2.B20
V9P0: J1.A18, J2.A3
VN3P4: J1.A19, J2.A2
VN22: J1.B19, J1.B20, J2.B1

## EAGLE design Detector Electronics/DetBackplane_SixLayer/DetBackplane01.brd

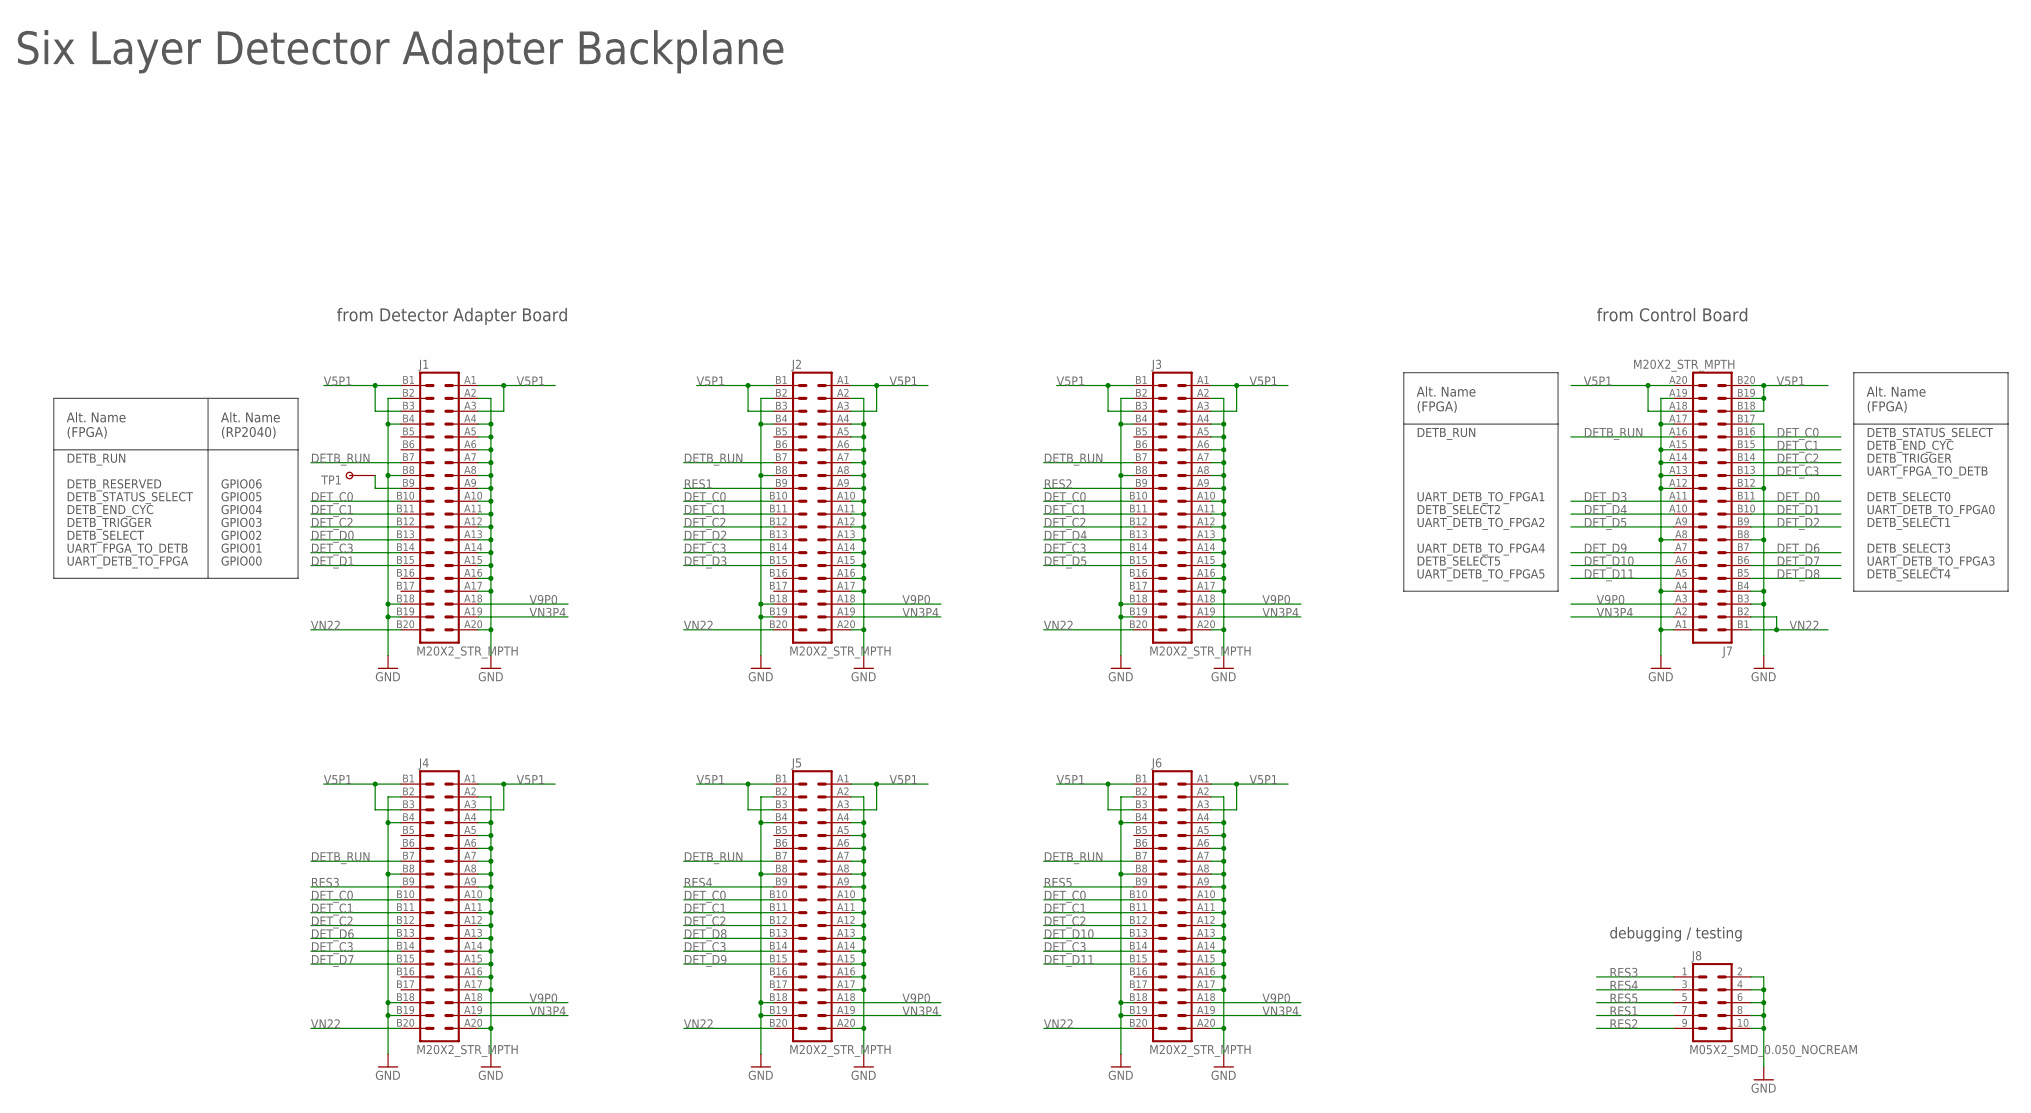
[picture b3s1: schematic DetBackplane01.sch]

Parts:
J1, J2, J3, J4, J5, J6, J7: M20X2_STR_MPTH; M20X2_HARFLEX_F_STR_MPTH
J8: M05X2_SMD_0.050_NOCREAM; M05X2_0.050_SMD_NO_CREAM
TP1: TESTPOINT_ROUND; TESTPAD_ROUND

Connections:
DETB_RUN: J1.B7 (13), J2.B7 (13), J3.B7 (13), J4.B7 (13), J5.B7 (13), J6.B7 (13), J7.A16 (32)
DET_C0: J1.B10 (19), J2.B10 (19), J3.B10 (19), J4.B10 (19), J5.B10 (19), J6.B10 (19), J7.B16 (31)
DET_C1: J1.B11 (21), J2.B11 (21), J3.B11 (21), J4.B11 (21), J5.B11 (21), J6.B11 (21), J7.B15 (29)
DET_C2: J1.B12 (23), J2.B12 (23), J3.B12 (23), J4.B12 (23), J5.B12 (23), J6.B12 (23), J7.B14 (27)
DET_C3: J1.B14 (27), J2.B14 (27), J3.B14 (27), J4.B14 (27), J5.B14 (27), J6.B14 (27), J7.B13 (25)
DET_D0: J1.B13 (25), J7.B11 (21)
DET_D1: J1.B15 (29), J7.B10 (19)
DET_D2: J2.B13 (25), J7.B9 (17)
DET_D3: J2.B15 (29), J7.A11 (22)
DET_D4: J3.B13 (25), J7.A10 (20)
DET_D5: J3.B15 (29), J7.A9 (18)
DET_D6: J4.B13 (25), J7.B7 (13)
DET_D7: J4.B15 (29), J7.B6 (11)
DET_D8: J5.B13 (25), J7.B5 (9)
DET_D9: J5.B15 (29), J7.A7 (14)
DET_D10: J6.B13 (25), J7.A6 (12)
DET_D11: J6.B15 (29), J7.A5 (10)
GND: J1.A2 (4), J1.A4 (8), J1.A5 (10), J1.A6 (12), J1.A7 (14), J1.A8 (16), J1.A9 (18), J1.A10 (20), J1.A11 (22), J1.A12 (24), J1.A13 (26), J1.A14 (28), J1.A15 (30), J1.A16 (32), J1.A17 (34), J1.A20 (40), J1.B2 (3), J1.B4 (7), J1.B8 (15), J1.B18 (35), J1.B19 (37), J2.A2 (4), J2.A4 (8), J2.A5 (10), J2.A6 (12), J2.A7 (14), J2.A8 (16), J2.A9 (18), J2.A10 (20), J2.A11 (22), J2.A12 (24), J2.A13 (26), J2.A14 (28), J2.A15 (30), J2.A16 (32), J2.A17 (34), J2.A20 (40), J2.B2 (3), J2.B4 (7), J2.B8 (15), J2.B18 (35), J2.B19 (37), J3.A2 (4), J3.A4 (8), J3.A5 (10), J3.A6 (12), J3.A7 (14), J3.A8 (16), J3.A9 (18), J3.A10 (20), J3.A11 (22), J3.A12 (24), J3.A13 (26), J3.A14 (28), J3.A15 (30), J3.A16 (32), J3.A17 (34), J3.A20 (40), J3.B2 (3), J3.B4 (7), J3.B8 (15), J3.B18 (35), J3.B19 (37), J4.A2 (4), J4.A4 (8), J4.A5 (10), J4.A6 (12), J4.A7 (14), J4.A8 (16), J4.A9 (18), J4.A10 (20), J4.A11 (22), J4.A12 (24), J4.A13 (26), J4.A14 (28), J4.A15 (30), J4.A16 (32), J4.A17 (34), J4.A20 (40), J4.B2 (3), J4.B4 (7), J4.B8 (15), J4.B18 (35), J4.B19 (37), J5.A2 (4), J5.A4 (8), J5.A5 (10), J5.A6 (12), J5.A7 (14), J5.A8 (16), J5.A9 (18), J5.A10 (20), J5.A11 (22), J5.A12 (24), J5.A13 (26), J5.A14 (28), J5.A15 (30), J5.A16 (32), J5.A17 (34), J5.A20 (40), J5.B2 (3), J5.B4 (7), J5.B8 (15), J5.B18 (35), J5.B19 (37), J6.A2 (4), J6.A4 (8), J6.A5 (10), J6.A6 (12), J6.A7 (14), J6.A8 (16), J6.A9 (18), J6.A10 (20), J6.A11 (22), J6.A12 (24), J6.A13 (26), J6.A14 (28), J6.A15 (30), J6.A16 (32), J6.A17 (34), J6.A20 (40), J6.B2 (3), J6.B4 (7), J6.B8 (15), J6.B18 (35), J6.B19 (37), J7.A1 (2), J7.A4 (8), J7.A8 (16), J7.A12 (24), J7.A13 (26), J7.A14 (28), J7.A15 (30), J7.A17 (34), J7.A19 (38), J7.B3 (5), J7.B4 (7), J7.B8 (15), J7.B12 (23), J7.B17 (33), J8.2, J8.4, J8.6, J8.8, J8.10
unnamed: J1.B9 (17), TP1.P$1
RES1: J2.B9 (17), J8.7
RES2: J3.B9 (17), J8.9
RES3: J4.B9 (17), J8.1
RES4: J5.B9 (17), J8.3
RES5: J6.B9 (17), J8.5
V5P1: J1.A1 (2), J1.A3 (6), J1.B1 (1), J1.B3 (5), J2.A1 (2), J2.A3 (6), J2.B1 (1), J2.B3 (5), J3.A1 (2), J3.A3 (6), J3.B1 (1), J3.B3 (5), J4.A1 (2), J4.A3 (6), J4.B1 (1), J4.B3 (5), J5.A1 (2), J5.A3 (6), J5.B1 (1), J5.B3 (5), J6.A1 (2), J6.A3 (6), J6.B1 (1), J6.B3 (5), J7.A18 (36), J7.A20 (40), J7.B18 (35), J7.B19 (37), J7.B20 (39)
V9P0: J1.A18 (36), J2.A18 (36), J3.A18 (36), J4.A18 (36), J5.A18 (36), J6.A18 (36), J7.A3 (6)
VN3P4: J1.A19 (38), J2.A19 (38), J3.A19 (38), J4.A19 (38), J5.A19 (38), J6.A19 (38), J7.A2 (4)
VN22: J1.B20 (39), J2.B20 (39), J3.B20 (39), J4.B20 (39), J5.B20 (39), J6.B20 (39), J7.B1 (1), J7.B2 (3)

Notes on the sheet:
Six Layer Detector Adapter Backplane
from Detector Adapter Board
from Control Board
GPIO00
GPIO01
GPIO02
GPIO03
GPIO04
GPIO05
GPIO06
UART_DETB_TO_FPGA
UART_FPGA_TO_DETB
DETB_SELECT
DETB_TRIGGER
DETB_END_CYC
DETB_STATUS_SELECT
DETB_RESERVED
DETB_RUN
debugging / testing
UART_DETB_TO_FPGA0
DETB_SELECT0
DETB_SELECT1
DETB_SELECT2
DETB_SELECT5
DETB_SELECT3
DETB_SELECT4
UART_DETB_TO_FPGA1
UART_DETB_TO_FPGA2
UART_DETB_TO_FPGA4
UART_DETB_TO_FPGA5
UART_DETB_TO_FPGA3
Alt. Name (FPGA)
Alt. Name (RP2040)

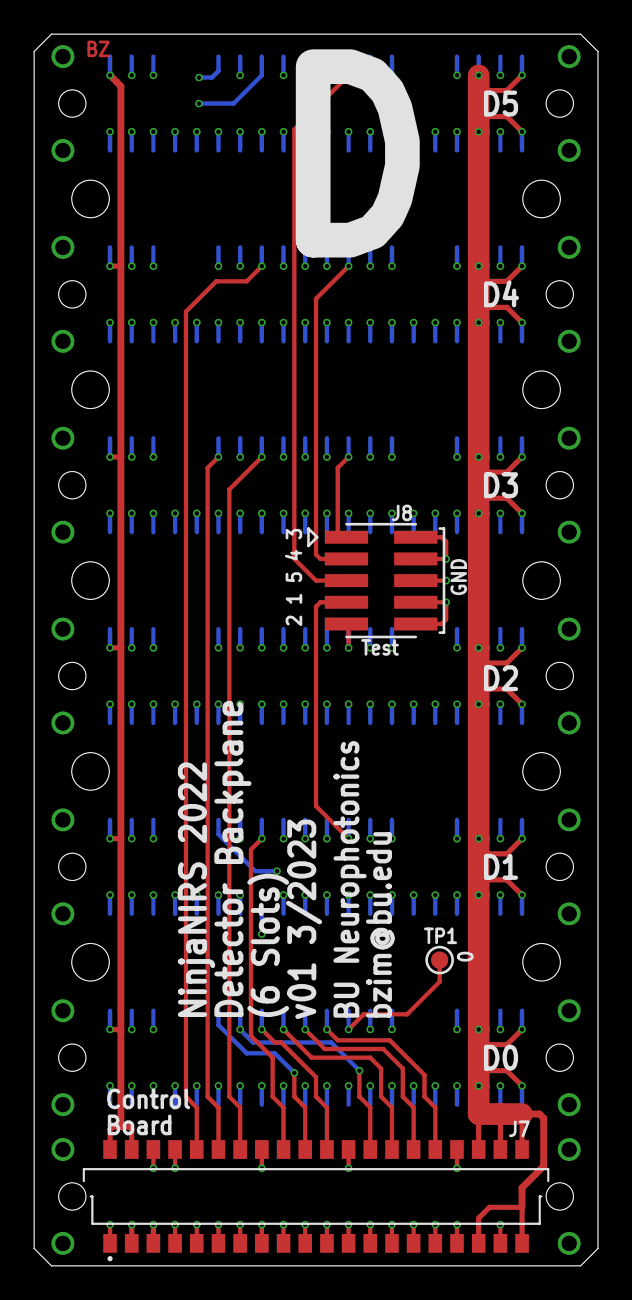
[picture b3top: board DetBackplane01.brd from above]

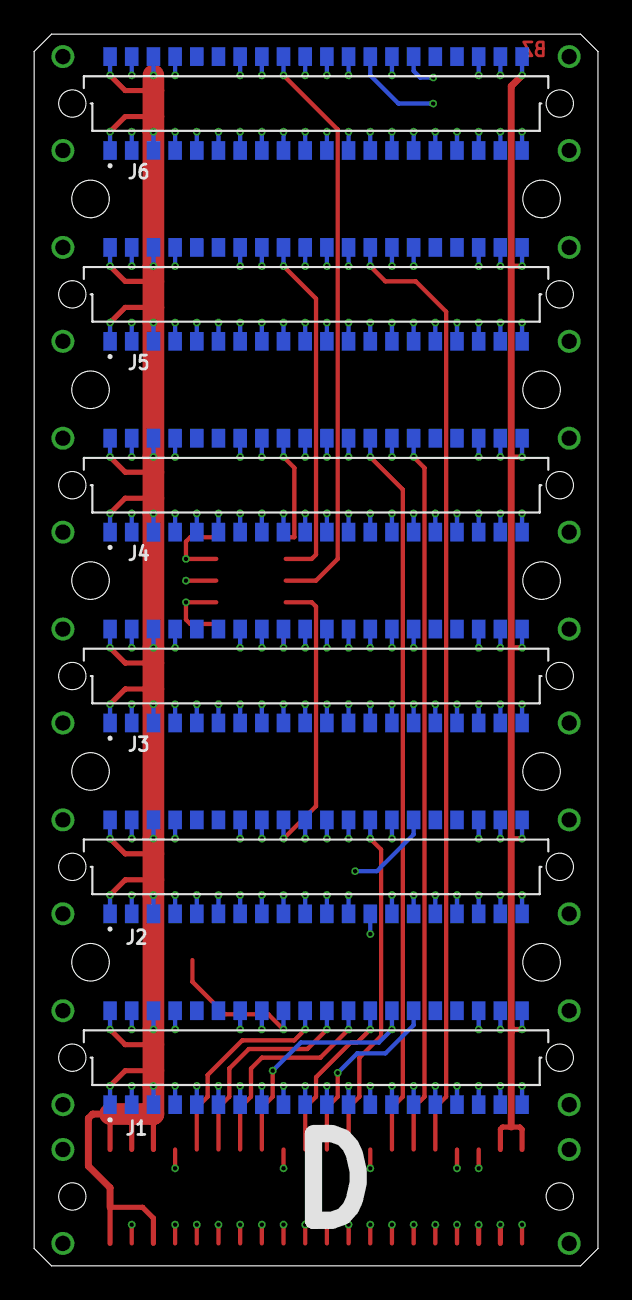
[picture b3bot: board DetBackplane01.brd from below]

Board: 4 copper layers, 33.0 x 72.1 mm, 9 parts (6 on the bottom side), 28 nets.

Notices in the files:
parts and their libraries:
SparkFun-Connectors: Licensing: Creative Commons ShareAlike 4.0 International - https://creativecommons.org/licenses/by-sa/4.0
